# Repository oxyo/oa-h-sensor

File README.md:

# Open Automation humidity sensor   

This is an Arduino UNO compatible device with HIH5031 humidity sensor installed.  
It uses [Ciseco XRF wireless RF radio UART serial data module][] to communicate with Open Automation Center

This simple device can measure air humidity up to 3% precision. Also provided option to connect SHARP GP2Y1010AU0F dust sensor to measure the dust concentration in air.
  
Arduino firmware, schematics and board files provided. 
  
For more information please visit [openautomation.center](http://openautomation.center)

Licensed under [WTFPL license terms](http://www.wtfpl.net/)

[Ciseco XRF wireless RF radio UART serial data module]: http://shop.ciseco.co.uk/xrf-wireless-rf-radio-uart-serial-data-module-xbee-shaped/

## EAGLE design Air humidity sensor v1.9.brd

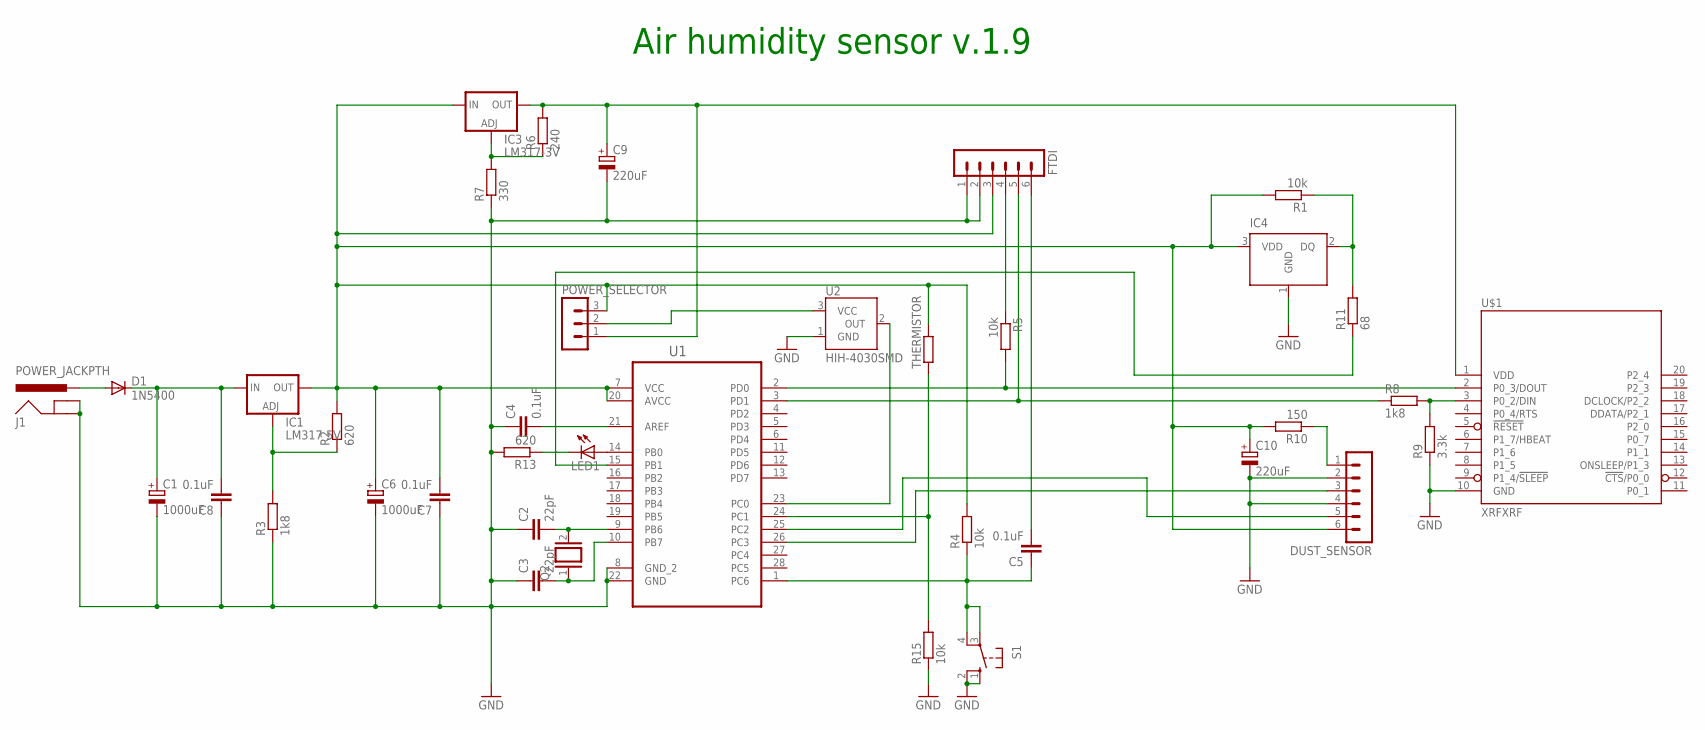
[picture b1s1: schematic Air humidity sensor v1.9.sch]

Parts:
C1, C6: 1000uF; E5-10,5
C2, C3: 22pF; C025-025X050
C4: 0.1uF; C075-032X103
C5, C7, C8: 0.1uF; C050-025X075
C9: 220uF; E3,5-8
C10: 220uF; E5-10,5
D1: 1N5400; DO201-15
DUST_SENSOR: MA06-1
FTDI: MA06-1
IC1: LM317 5V; 317TS
IC3: LM317-3V; 317TS
IC4: DS1820; TO-92
J1: POWER_JACKPTH; POWER_JACK_PTH
LED1: LED3MM
POWER_SELECTOR: MA03-1
Q2: XTAL/S; QS
R1, R4, R5, R15: 10k; 0207/5V
R2: 620; 0207/5V
R3: 1k8; 0207/5V
R6: 240; 0207/5V
R7: 330; 0207/5V
R8: 1k8; 0207/12
R9: 3.3k; 0207/12
R10: 150; 0207/5V
R11: 68; 0207/12
R13: 620; 0207/12
S1: 10-XX; B3F-10XX
THERMISTOR: R-EU_0207/5V; 0207/5V
U1: ATMEGA328P-PU; DIP254P762X457-28
U2: HIH-4030SMD; HIH-4030
U$1: XRFXRF; XRF

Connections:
GND: C1.-, C2.1, C3.1, C4.1, C6.-, C7.1, C8.1, C9.-, C10.-, DUST_SENSOR.2, DUST_SENSOR.4, FTDI.1, FTDI.2, IC4.1 (GND), J1.GND, J1.GNDBREAK, R3.1, R7.1, R9.1, R13.2, R15.1, S1.1 (S), S1.2 (S1), U1.8 (GND_2), U1.22 (GND), U2.1 (GND), U$1.10 (GND)
LM317-5V: IC1.1 (ADJ), R2.1, R3.2
unnamed: C4.2, U1.21 (AREF)
unnamed: C5.2, FTDI.6
unnamed: DUST_SENSOR.5, U1.25 (PC2)
unnamed: DUST_SENSOR.3, U1.26 (PC3)
unnamed: R15.2, THERMISTOR.1, U1.24 (PC1)
unnamed: C9.+, IC3.2 (OUT), POWER_SELECTOR.1, R6.2, U$1.1 (VDD)
unnamed: C6.+, C7.2, C10.+, DUST_SENSOR.6, FTDI.3, IC1.2 (OUT), IC3.3 (IN), IC4.3 (VDD), POWER_SELECTOR.3, R1.2, R2.2, R4.2, R10.2, THERMISTOR.2, U1.7 (VCC), U1.20 (AVCC)
unnamed: D1.A, J1.PWR
unnamed: U1.23 (PC0), U2.2 (OUT)
unnamed: C1.+, C8.2, D1.C, IC1.3 (IN)
unnamed: C2.2, Q2.2, U1.9 (PB6)
unnamed: C3.2, Q2.1, U1.10 (PB7)
unnamed: C5.1, R4.1, S1.3, S1.4 (P1), U1.1 (PC6)
unnamed: FTDI.4, R5.1
unnamed: R5.2, U1.2 (PD0), U$1.2 (P0_3/DOUT)
unnamed: FTDI.5, R8.1, U1.3 (PD1)
unnamed: IC3.1 (ADJ), R6.1, R7.2
unnamed: R8.2, R9.2, U$1.3 (P0_2/DIN)
unnamed: POWER_SELECTOR.2, U2.3 (VCC)
unnamed: IC4.2 (DQ), R1.1, R11.2
unnamed: R11.1, U1.15 (PB1)
unnamed: DUST_SENSOR.1, R10.1
unnamed: LED1.K (C), R13.1
unnamed: LED1.A, U1.14 (PB0)

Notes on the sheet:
Air humidity sensor v.1.9

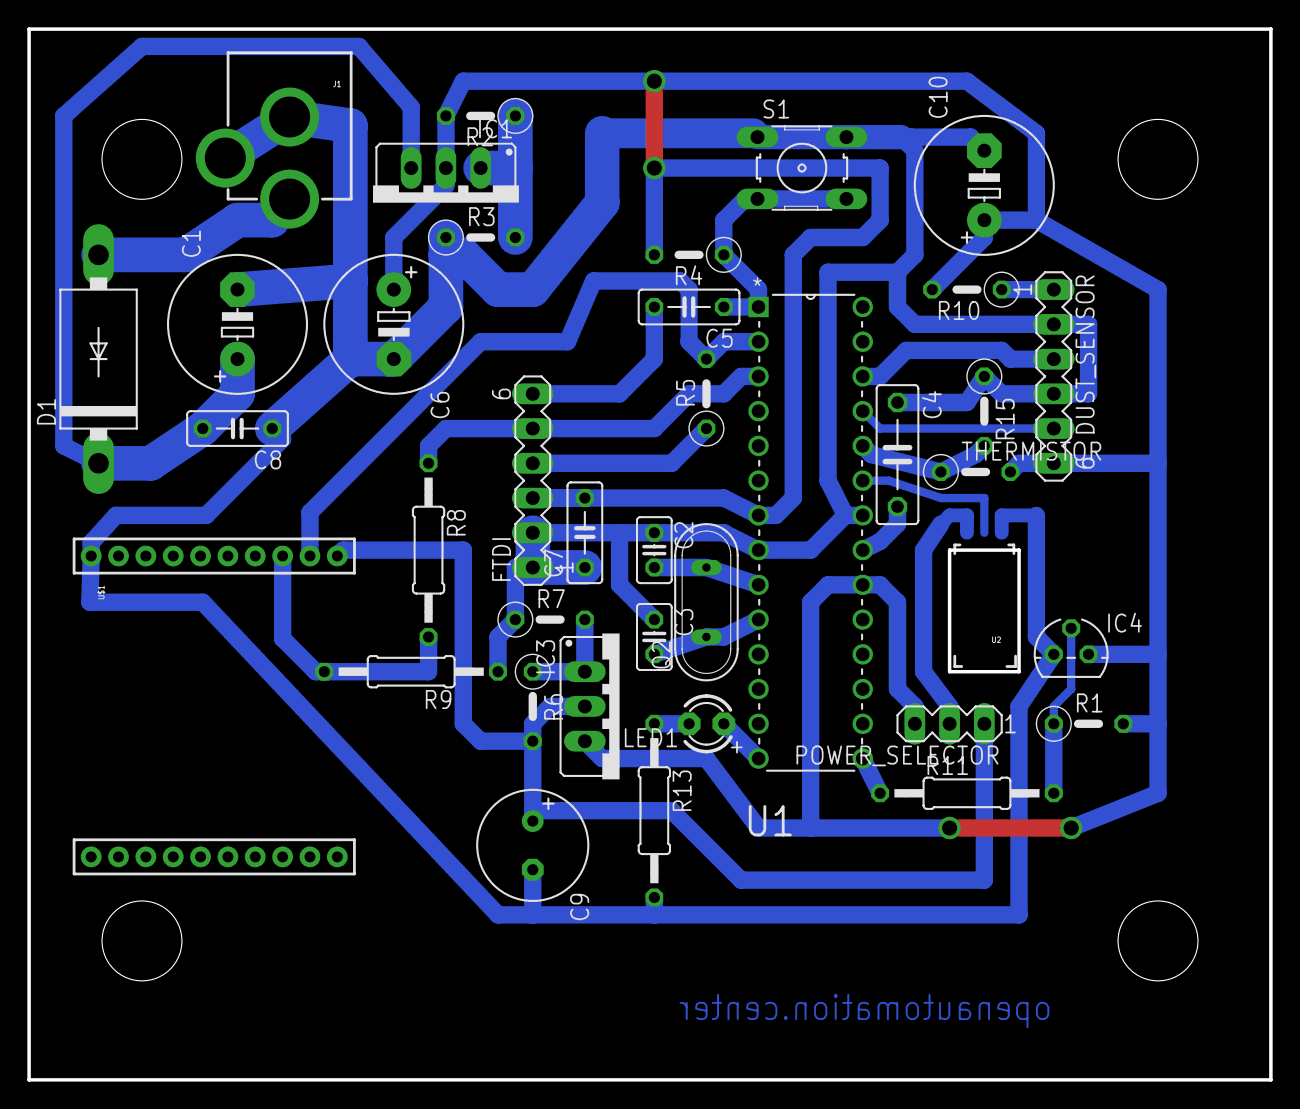
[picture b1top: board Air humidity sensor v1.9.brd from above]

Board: 2 copper layers, 90.8 x 76.8 mm, 38 parts (0 on the bottom side), 26 nets.

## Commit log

2015-03-30 Update LICENSE

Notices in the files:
parts and their libraries:
SparkFun-Connectors: Licensing: CC v3.0 Share-Alike You are welcome to use this library for commercial purposes.
